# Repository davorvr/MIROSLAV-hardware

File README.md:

</img>
<br> MIROSLAV hardware <br>
  <br clear="left"/>
========

### What is it?

This repo holds everything needed to build a working MIROSLAV device. Arduino firmware and Record-a-SLAV, a Python data acquisition script, can be found in the [`MIROSLAV-firmware` repository](https://github.com/davorvr/MIROSLAV-firmware). A complete, user-friendly MIROSLAV software toolkit for analysis of MIROSLAV data, from raw data to statistical analysis, can be found in the [`MIROSLAV-analysis` repository](https://github.com/davorvr/MIROSLAV-analysis) - also contains an example dataset of real data recorded in our lab.

### What is MIROSLAV, anyway?

**MIROSLAV (_Multicage InfraRed Open Source Locomotor Activity eValuator_)** is a platform for non-invasive monitoring of circadian locomotor activity in laboratory rodents. MIROSLAV is fully open source and scalable to hundreds of cages. All of its hardware and software components are described in the paper: #url

***

### File tree

- `bom/` - Bill of Materials for all needed parts and an informative order sheet for the PCBs. Note that the PCBs are panelised so e.g. 10 pcs of the sensor board refer to 10x2 panels - total 200 boards.

- `gerbers/` - Last produced gerber files - MIROSLAV v0.4, as described in the paper

- KiCad board project directories:
  - `main_board/`
  - `power_board/`
  - `sensor_board/`
  - `serialization_board/`

- `symbols/` - Contains additional individual symbols and footprints used.

- `miro-v04.pretty/` - Contains additional symbols, packed into a `.pretty` library (footprints)

- `miro-v04.kicad_sym` - Contains additional symbols, packed into a `.kicad_sym` library (schematic symbols)

### About the current state of the designs

**This version now uses a different ESP32-S2 module - it is not compatible with ESP32-S2-Saola-1 used in v0.4!**

Current MIROSLAV hardware revision is v0.5 - the main objective was to produce a board that works with ESP32-S2-DevKitM-1 as it seems that Espressif doesn't produce ESP32-S2-Saola-1 boards anymore. Other than that, it's just a few QoL improvements. If you need a Saola-compatible board, the v0.4 still works well. v0.5 hasn't been produced and tested yet.

To produce MIROSLAV, it is sufficient to generate Gerber files and send them to a PCB manufacturer.

Additional part symbols and footprints used in the design are contained in `miro-v04.kicad_sym` and `miro-v04.pretty` libraries, respectively. [Espressif's KiCad library v3.0.0](https://github.com/espressif/kicad-libraries) was used for the ESP32-S2-DevKitM-1 footprint.

### Changelog

Here is a full list of changes since the first published version, v0.4:

* MAINBOARD: Modified the mainboard to use ESP32-S2-DevKitM-1 instead of ESP32-S2-Saola-1. Footprints can be obtained from [Espressif's KiCad footprint library repository](https://github.com/espressif/kicad-libraries).
* MAINBOARD: Expanded to the right and repositioned environmental sensors along the right edge of the board to stay out of the way of the ESP32 board's USB connector. The sensor sockets are also farther apart so they don't clash.
* MAINBOARD: Added M3 mounting holes, the "I2C PIR" connector and resistor "R1" have been moved slightly to accomodate them.
* POWERBOARD: Added M3 mounting holes, the board is wider as a result.

### Last produced design

MIROSLAV's last produced and tested design was also its first published hardware revision, v0.4, designed in Dec 2021 in KiCad 6.0, and can be found in this repository, [under the tag "v0.4"](https://github.com/davorvr/MIROSLAV-hardware/tree/v0.4). At that time, we generated Gerbers (which are still available under the v0.4 tag) and produced the PCBs through JLCPCB. The v0.4 devices have been successfully in the proof-of-concept study described in the MIROSLAV paper.

### Related repositories

* [`MIROSLAV-firmware`](https://github.com/davorvr/MIROSLAV-firmware) - Arduino firmware and Record-a-SLAV, a Python data acquisition script. Once you build the device, you need to flash the firmware, set up an MQTT broker, and run Record-a-SLAV on a PC to start recording data.
* [`mirofile`](https://github.com/davorvr/mirofile) - Your buddy for dealing with raw MIROSLAV data. A Python library used by Prepare-a-SLAV to parse raw MIROSLAV logs into a dataframe.
* [`MIROSLAV-analysis`](https://github.com/davorvr/MIROSLAV-analysis) - A complete, user-friendly MIROSLAV software toolkit for analysis of MIROSLAV data, from raw data to statistical analysis. Also contains an example dataset with real data recorded in our lab.

### License

You can modify any part of MIROSLAV freely under the **GPLv3** license - if you have any questions, problems, or ideas on how to improve MIROSLAV, feel free to reach out to us, submit a GitHub issue, or a pull request.

The MIROSLAV logo is created by Petra Šoštarić Mužić and licensed under the **CC BY-NC-SA 4.0** license - more details can be found in the repository's [`logo/` directory](logo/).

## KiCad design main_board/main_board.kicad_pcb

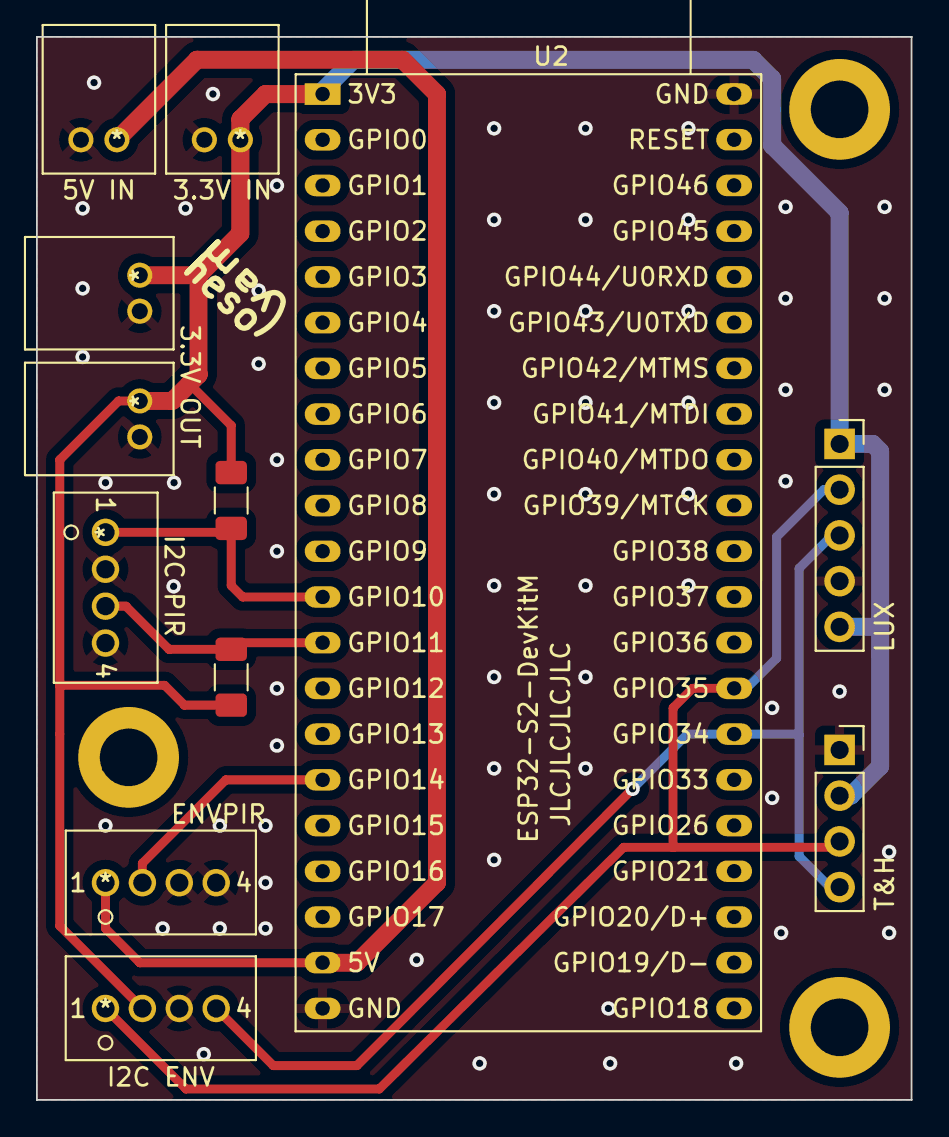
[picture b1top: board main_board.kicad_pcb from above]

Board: 2 copper layers, 48.6 x 59.1 mm, 12 parts (0 on the bottom side), 8 nets.

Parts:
J1: 5V IN; TE_HDI_2_horiz
J2: 3.3V IN; TE_HDI_2_horiz
J3: I2C PIR; TE_HDI_4_vert
J4, J5: 3.3V OUT; TE_HDI_2_horiz
J12: I2C ENV; TE_HDI_4_vert
J13: ENVPIR; TE_HDI_4_vert
LUX: BH1750 (lux); PinSocket_1x05_P2.54mm_Vertical
R1, R2: 1k; R_1206_3216Metric_Pad1.30x1.75mm_HandSolder
T&H: HDC1080 (temp&hum); PinSocket_1x04_P2.54mm_Vertical
U2: ESP32-S2-DevKitM

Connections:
+3V3: J2.1, J4.1, J5.1, J12.2, LUX.1, LUX.5, R1.2, R2.1, T&H.2, U2.1 (3V3)
+5V: J1.1, J13.1, U2.20 (5V0)
/ENVPIR_DIN: J13.2, U2.16 (GPIO14/TOUCH14/ADC2_CH3/FSPIWP/FSPIDQS)
/ENV_SCL: J12.4, LUX.3, T&H.4, U2.28 (GPIO34)
/ENV_SDA: J12.1, LUX.2, T&H.3, U2.29 (GPIO35)
/PIR_SCL: J3.3, R1.1, U2.13 (GPIO11/TOUCH11/ADC2_CH0/FSPID/FSPIIO5)
/PIR_SDA: J3.1, R2.2, U2.12 (GPIO10/TOUCH10/ADC1_CH9/FSPICS0/FSPIIO4)
GND: J1.2, J2.2, J3.2, J3.4, J4.2, J5.2, J12.3, J13.3, J13.4, LUX.4, T&H.1, U2.21 (GND), U2.42 (GND)

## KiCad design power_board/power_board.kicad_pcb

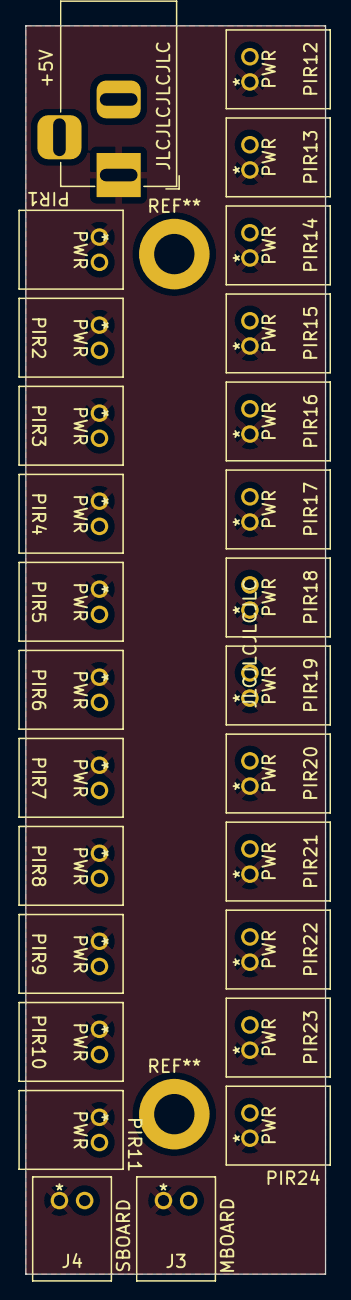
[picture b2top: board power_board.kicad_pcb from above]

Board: 2 copper layers, 23.8 x 99.1 mm, 27 parts (0 on the bottom side), 2 nets, no tracks yet.

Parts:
+5V: PWR IN; BarrelJack_Horizontal
J3: MBOARD; TE_HDI_2_horiz_altsilk
J4: SBOARD; TE_HDI_2_horiz_altsilk
PIR1, PIR2, PIR3, PIR4, PIR5, PIR6, PIR7, PIR8, PIR9, PIR10, PIR11, PIR12, PIR13, PIR14, PIR15, PIR16, PIR17, PIR18, PIR19, PIR20, PIR21, PIR22, PIR23, PIR24: PWR; TE_HDI_2_horiz_altsilk

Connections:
+5V: +5V.1, J3.1, J4.1, PIR1.1, PIR2.1, PIR3.1, PIR4.1, PIR5.1, PIR6.1, PIR7.1, PIR8.1, PIR9.1, PIR10.1, PIR11.1, PIR12.1, PIR13.1, PIR14.1, PIR15.1, PIR16.1, PIR17.1, PIR18.1, PIR19.1, PIR20.1, PIR21.1, PIR22.1, PIR23.1, PIR24.1
GND: +5V.2, +5V.3, J3.2, J4.2, PIR1.2, PIR2.2, PIR3.2, PIR4.2, PIR5.2, PIR6.2, PIR7.2, PIR8.2, PIR9.2, PIR10.2, PIR11.2, PIR12.2, PIR13.2, PIR14.2, PIR15.2, PIR16.2, PIR17.2, PIR18.2, PIR19.2, PIR20.2, PIR21.2, PIR22.2, PIR23.2, PIR24.2

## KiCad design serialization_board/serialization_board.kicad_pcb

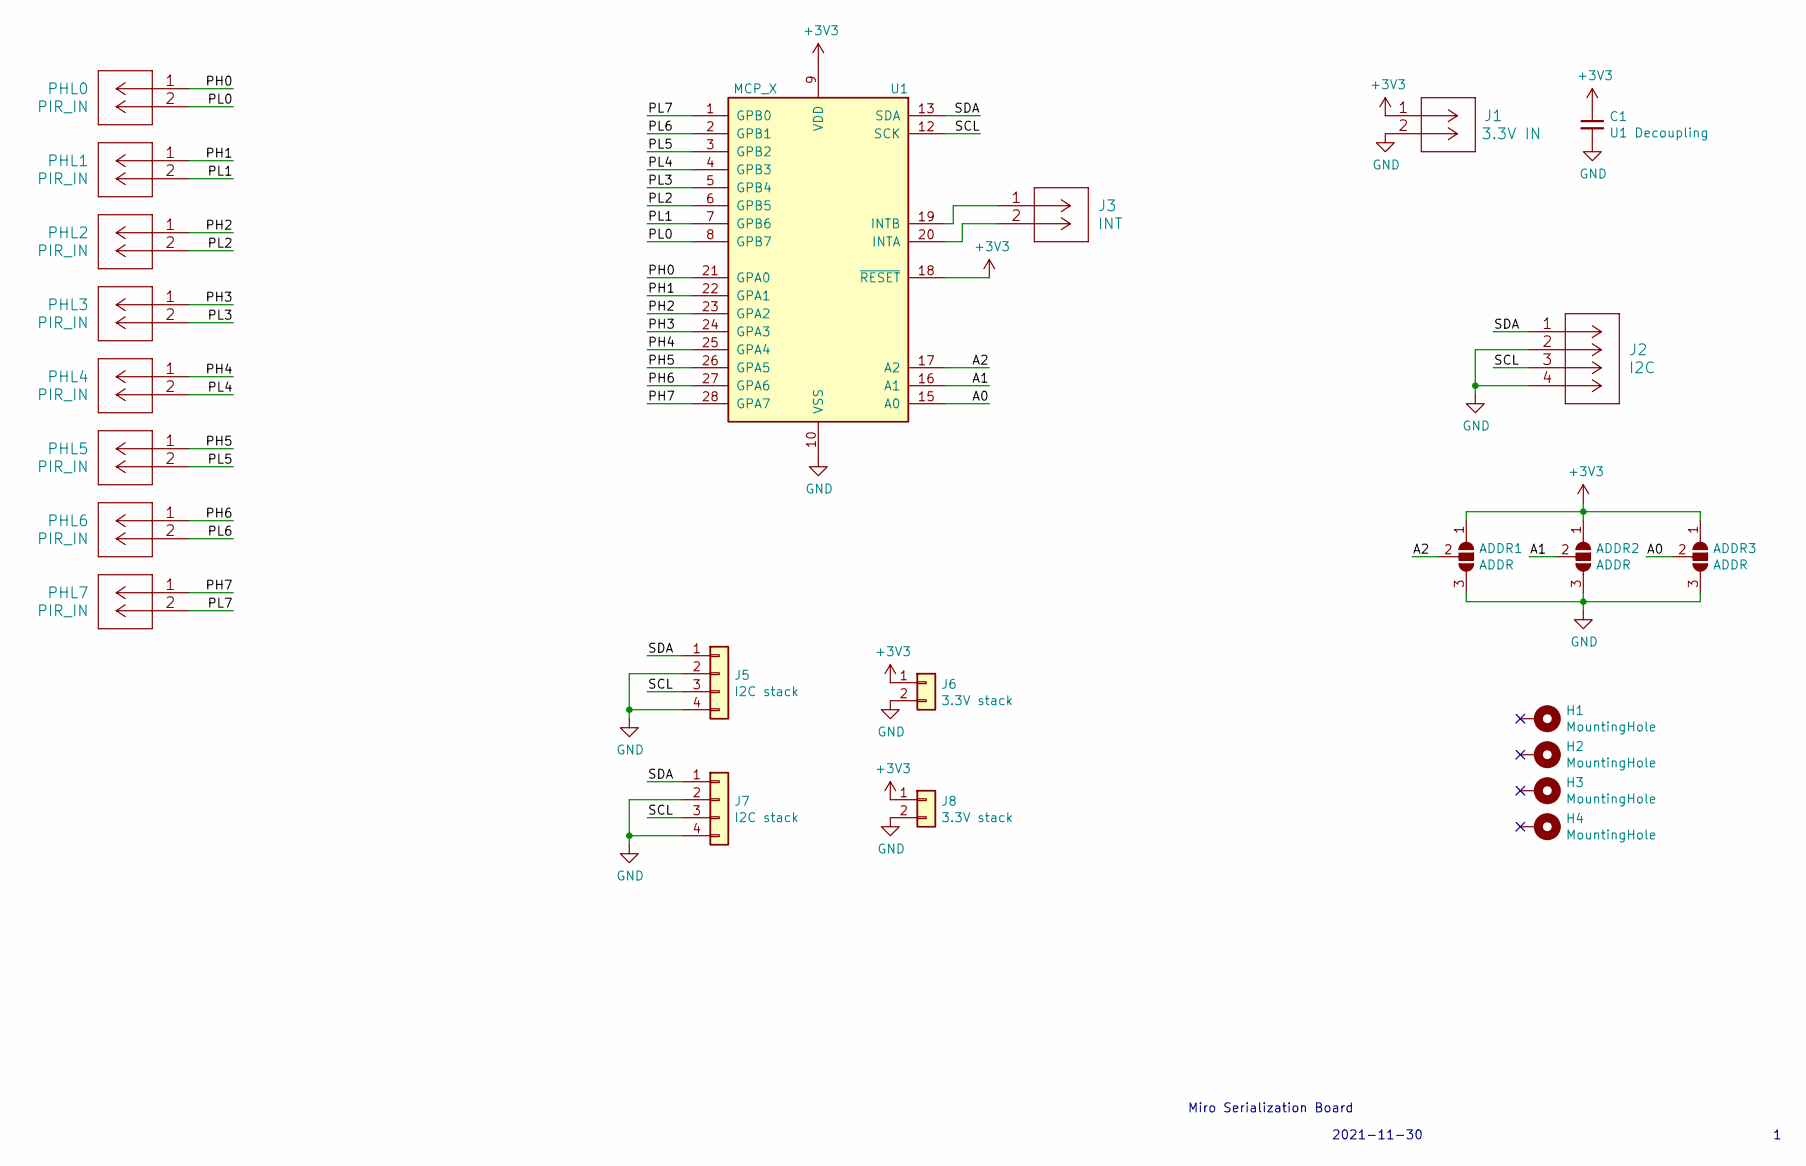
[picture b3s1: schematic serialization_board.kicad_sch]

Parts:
ADDR1, ADDR2, ADDR3: ADDR; SolderJumper-3_P1.3mm_Open_Pad1.0x1.5mm_NumberLabels
C1: U1 Decoupling; C_1206_3216Metric_Pad1.33x1.80mm_HandSolder
H1, H2, H3, H4: MountingHole; MountingHole_4.3mm_M4_ISO14580_Pad
J1: 3.3V IN; TE_HDI_2_horiz
J2: I2C; TE_HDI_4_vert
J3: INT; TE_HDI_2_horiz
J5: I2C stack; PinSocket_1x04_P2.54mm_Vertical
J6: 3.3V stack; PinSocket_1x02_P2.54mm_Vertical
J7: I2C stack; PinHeader_1x04_P2.54mm_Vertical
J8: 3.3V stack; PinHeader_1x02_P2.54mm_Vertical
PHL0, PHL1, PHL2, PHL3, PHL4, PHL5, PHL6, PHL7: PIR_IN; TE_HDI_2_horiz
U1: MCP_X; DIP-28_W7.62mm

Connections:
/A0: ADDR3.2 (C), U1.15 (A0)
/A1: ADDR2.2 (C), U1.16 (A1)
/A2: ADDR1.2 (C), U1.17 (A2)
/PH0: PHL0.1, U1.21 (GPA0)
/PH1: PHL1.1, U1.22 (GPA1)
/PH2: PHL2.1, U1.23 (GPA2)
/PH3: PHL3.1, U1.24 (GPA3)
/PH4: PHL4.1, U1.25 (GPA4)
/PH5: PHL5.1, U1.26 (GPA5)
/PH6: PHL6.1, U1.27 (GPA6)
/PH7: PHL7.1, U1.28 (GPA7)
/PL0: PHL0.2, U1.8 (GPB7)
/PL1: PHL1.2, U1.7 (GPB6)
/PL2: PHL2.2, U1.6 (GPB5)
/PL3: PHL3.2, U1.5 (GPB4)
/PL4: PHL4.2, U1.4 (GPB3)
/PL5: PHL5.2, U1.3 (GPB2)
/PL6: PHL6.2, U1.2 (GPB1)
/PL7: PHL7.2, U1.1 (GPB0)
/SCL: J2.3, J5.3, J7.3, U1.12 (SCK); also elsewhere on the board
/SDA: J2.1, J5.1, J7.1, U1.13 (SDA); also elsewhere on the board
GND: ADDR1.3 (B), ADDR2.3 (B), ADDR3.3 (B), C1.2, J1.2, J2.2, J2.4, J5.2, J5.4, J6.2, J7.2, J7.4, J8.2, U1.10 (VSS); also elsewhere on the board
unnamed: J3.1, U1.19 (INTB)
unnamed: J3.2, U1.20 (INTA)

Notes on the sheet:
Miro Serialization Board
2021-11-30

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
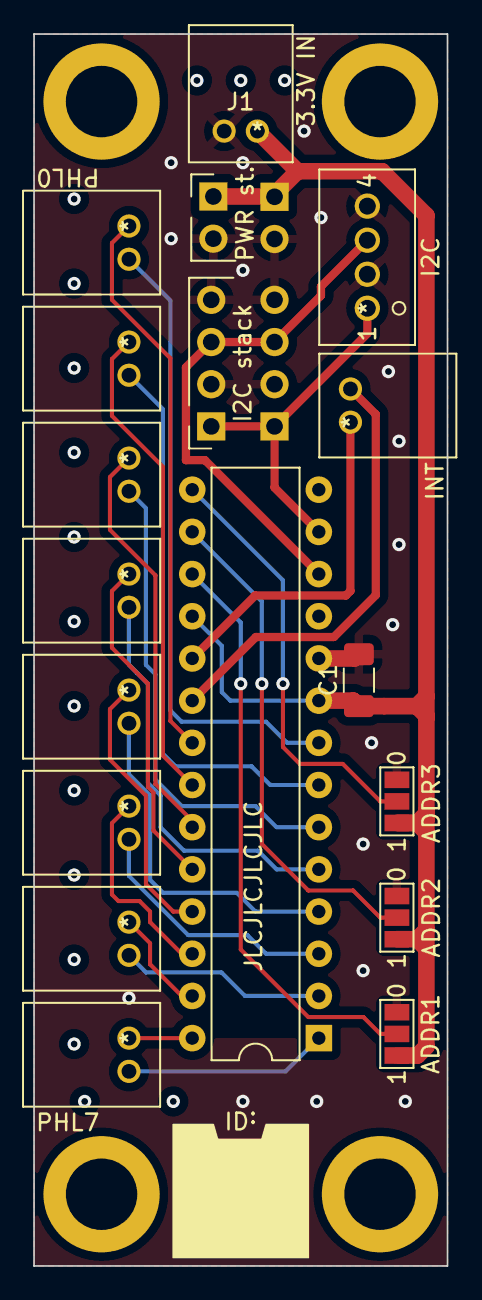
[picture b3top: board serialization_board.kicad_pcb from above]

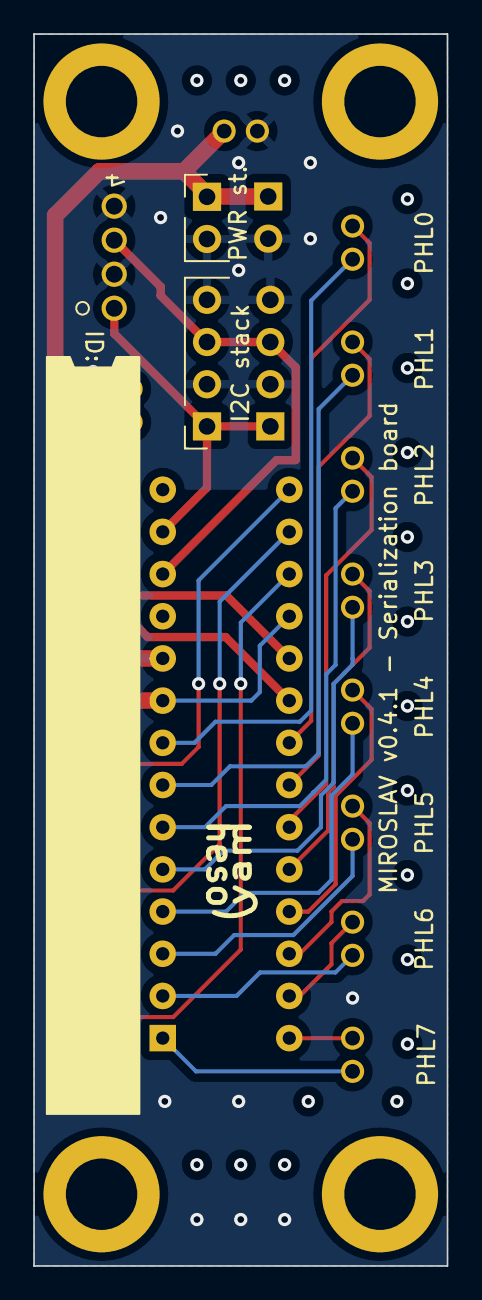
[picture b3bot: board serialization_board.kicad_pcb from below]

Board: 2 copper layers, 24.9 x 74.2 mm, 24 parts (2 on the bottom side), 25 nets.

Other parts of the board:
I2C stack: I2C stack; PinSocket_1x04_P2.54mm_Vertical
PWR st.: 3.3V stack; PinHeader_1x02_P2.54mm_Vertical

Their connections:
/SCL: I2C stack.3; also elsewhere on the board
/SDA: I2C stack.1; also elsewhere on the board
GND: I2C stack.2, I2C stack.4, PWR st..2; also elsewhere on the board

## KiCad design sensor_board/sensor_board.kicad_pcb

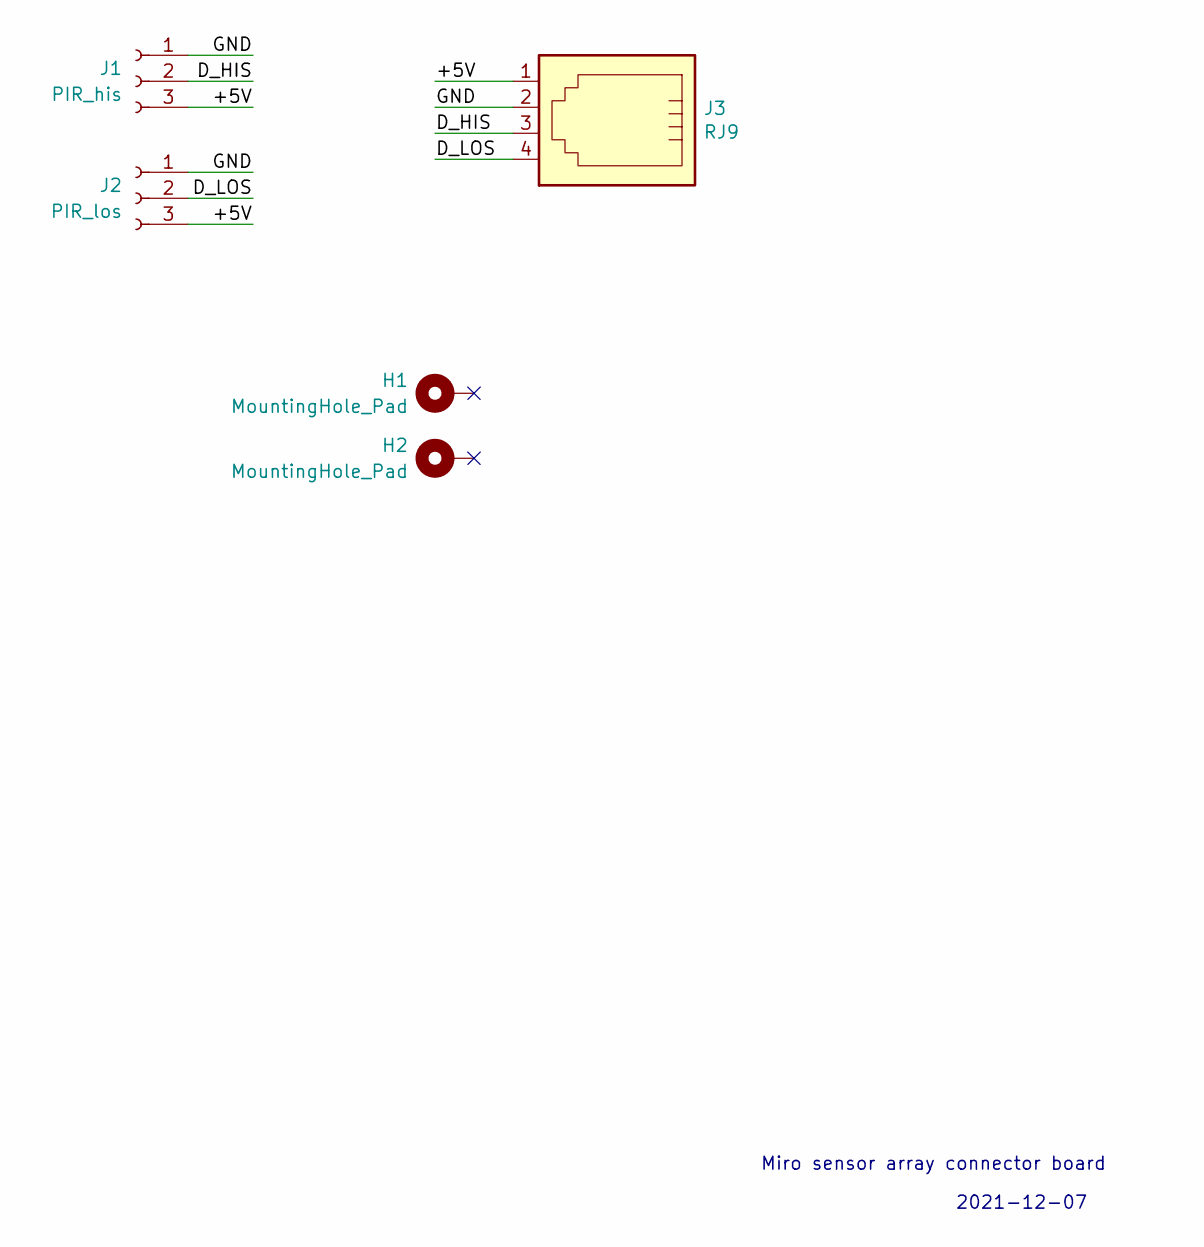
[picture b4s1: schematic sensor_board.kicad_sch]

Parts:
H1: MountingHole_Pad; MountingHole_4.3mm_M4_ISO14580_Pad
H2: MountingHole_Pad; MountingHole_4.3mm_M4_ISO14580_Pad_OVAL
J1: PIR_his; PinSocket_1x03_P2.54mm_Vertical
J2: PIR_los; PinSocket_1x03_P2.54mm_Vertical
J3: RJ9; 4P4C_RJ9_vert

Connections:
/+5V: J1.3, J2.3, J3.1
/D_HIS: J1.2, J3.3
/D_LOS: J2.2, J3.4
/GND: J1.1, J2.1, J3.2

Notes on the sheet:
Miro sensor array connector board
2021-12-07

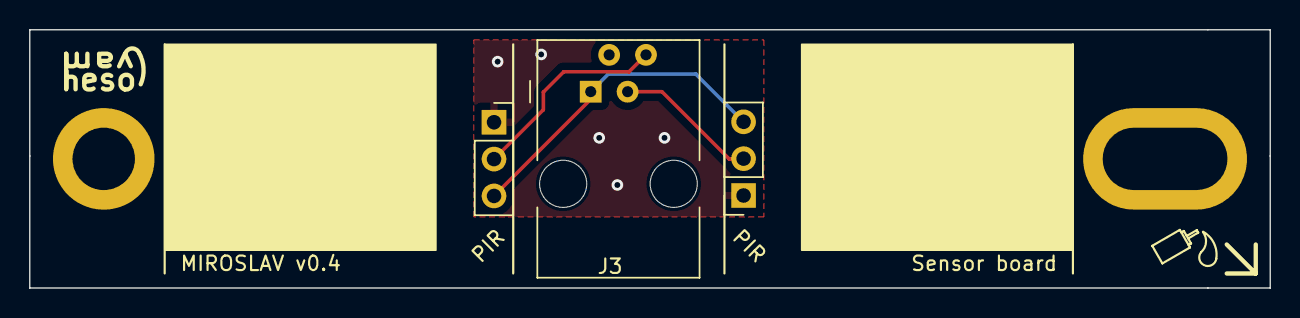
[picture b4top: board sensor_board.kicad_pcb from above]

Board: 2 copper layers, 85.5 x 17.8 mm, 5 parts (0 on the bottom side), 4 nets.

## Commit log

2024-06-17 Set proper revision date on POWERBOARD
2024-06-19 Some fixes and v0.5 labels
2024-06-19 Added BOM and updated README
2024-06-20 Specified decoupling cap value
2024-06-20 Added SMD parts to BOM
2024-06-20 Fixed BOM
2024-07-06 Added logo and paper URL
2024-07-06 Update README.md
    Fixed Zenodo DOI

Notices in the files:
parts and their libraries:
Copyright 2021 Accelerated Designs. All rights reserved.
